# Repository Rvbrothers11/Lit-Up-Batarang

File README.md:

# Lit-Up-Batarang
A Project where I modelled a batarang with LEDs using a PCB in KiCad

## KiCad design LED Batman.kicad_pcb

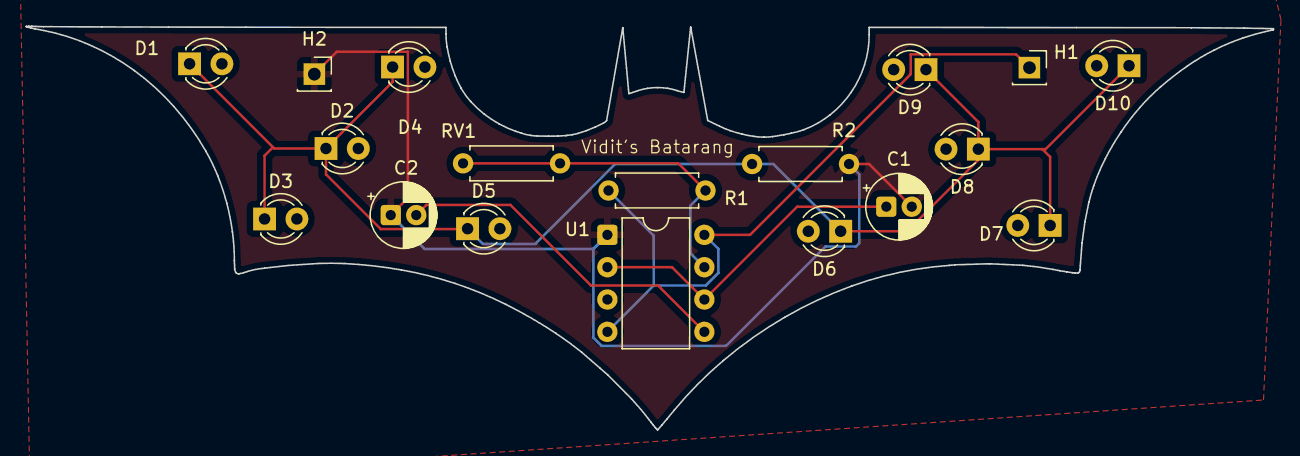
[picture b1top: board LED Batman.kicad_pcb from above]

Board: 2 copper layers, 98.0 x 31.7 mm, 18 parts (0 on the bottom side), 6 nets.

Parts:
C1: C_Polarized; CP_Radial_D5.0mm_P2.00mm
C2: C; CP_Radial_D5.0mm_P2.00mm
D1, D2, D3, D4, D5, D6, D7, D8, D9, D10: LED; LED_D3.0mm
H1, H2: MountingHole_Pad; PinSocket_1x01_P2.54mm_Vertical
R1, R2: R; R_Axial_DIN0207_L6.3mm_D2.5mm_P7.62mm_Horizontal
RV1: 50k; R_Axial_DIN0207_L6.3mm_D2.5mm_P7.62mm_Horizontal
U1: NE555P; DIP-8_W7.62mm

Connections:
+5V: H1.1, R1.1, U1.4 (~RST), U1.8 (VCC)
GND: C1.2, C2.1, H2.1, R2.2, U1.1 (GND)
unnamed: D1.1 (K), D2.1 (K), D3.1 (K), D4.1 (K), D5.1 (K), D6.1 (K), D7.1 (K), D8.1 (K), D9.1 (K), D10.1 (K), R2.1
unnamed: C2.2, U1.5 (CONT)
unnamed: R1.2, RV1.1, RV1.2, U1.7 (DISCH)
TR: C1.1, U1.2 (TRIG), U1.6 (THRES)
